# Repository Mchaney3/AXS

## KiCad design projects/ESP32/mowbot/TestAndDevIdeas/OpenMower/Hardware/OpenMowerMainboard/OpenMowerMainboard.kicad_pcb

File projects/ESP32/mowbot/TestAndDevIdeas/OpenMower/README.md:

# OpenMower

## Join the Discord server for OpenMower discussion: 

# About the Project
**:warning: DISCLAIMER:**

**IF YOU ARE NOT 100% SURE WHAT YOU ARE DOING, PLEASE DON'T TRY THIS AT HOME!**

**This repo is still WIP. The robot works though, I just need to make hardware and software pretty, so just :star: star and 👀 watch the repository if you want updates!**

Let's be honest: The current generation of robotic lawn mowers sucks. Basically all of these bots drive in a random direction until they hit the border of the lawn, rotate for a randomized duration and repeat. **I think we can do better!**

Therefore, we have disassembled the cheapest off-the-shelf robotic mower  we could find (YardForce Classic 500) and were surprised that the hardware itself is actually quite decent:
- Geared sensored brushless motors for the wheels
- A sensored brushless motor for the mower motor itself
- The whole construction seems robust, waterproof and all in all thought through
- All components are connected using standard connectors, therefore upgrading the hardware is easily possible.

The bottom line is: The bot itself is surprisingly high quality and doesn't need to be changed at all. **We just need some better software in there**.

# Project Goals

Here is a quick overview of this project's goals:

:heavy_check_mark: **Autonomous Lawn Mowing:** Obviously, the device should be able to mow the lawn automatically.

:heavy_check_mark: **Good Safety:** The device must be safe, e.g. emergency stop if lifted or crashed.

:heavy_check_mark: **No Perimeter Wire Needed:** We want to be flexible and support multiple mowing areas.

:heavy_check_mark: **Low Cost:** It should be cheaper than a mid range off-the-shelf product

:heavy_check_mark: **Open Source:** I want to share knowledge and enable others to build an OpenMower as well.

:heavy_check_mark: **Nice to Look At:** You should not be ashamed to have an OpenMower mowing your lawn.

:heavy_check_mark: **Avoid Obstacles:** The mower should detect obstacles and avoid them during mowing.

:heavy_check_mark: **Rain Detection:** The device should be able to detect bad weather conditions and pause mowing until they improve.

# Current State

It's not really *that easy* to upgrade the robot, since unfortunately the mainboard used by those bots is proprietary. Therefore the first step is to create a mainboard which then can be used to deploy some better software later on. This is what we are currently working on.

## Hardware

The first mainboard PCB is almost done. It currently looks like this:

### Hardware To-Do:

- [ ] Low Level Firmware Implementation
  - [x] Voltage / Current Sense
  - [x] Emergency Stop Button tracking
  - [x] IMU Communication
  - [x] Rain Sensor
  - [x] Charging State
  - [ ] Sound Module
  - [ ] UI Board Communication
  - [ ] Low Power Mode
- [ ] ROS Hardware Interface
- [ ] Hardware Redesign (bugs / enhancements):
  - [ ] Digial Emergency Stop Signal from Pico to xESC
  - [ ] Sound Module Pinout needs to be adapted to DFPlayer
  - [ ] XT60 Power Connector needs to be connected to main power instead of charging input

# Software

The basic software is basically done; Our prototype works as intended (but is not able to avoid obstacles yet).

The software for the robot can be found in a separate repository: https://github.com/ClemensElflein/open_mower_ros

### Software To-Do:

- [x] Mowing State Machine (Docking / Mowing, ...)
- [x] Path Planning
- [ ] Obstacle Avoidance
- [ ] App / Visualization

# How You Can Help

The project is currently much more advanced than it might currently look on this page. The prototype below is able to mow our lawn without problems. **But the documentation is missing.**

Therefore, at the current state, you can only wait until I have uploaded all code and documentation to this repository. **Star this repository in order to get updates!**

## Compatible Robotic Mowers

While disassembling the bot, I wondered about its mainboard: Instead of "YardForce" it read "GForce". After checking the internet for "GForce" robots, I found that that very similar looking robotic mowers are sold under the Herkules brand. Naturally I tried to dig deeper and actually found evidence that the mainboard is manufactured by some chinese company (SUMTEC Hardware).

It is therefore quite safe to assume that many robot mowers are **basically the same device in a different case**. This would be a huge win for the community, since this would mean that by making one of those robots smarter, we could upgrade **A LOT OF ROBOTS!**

Therefore it might be a good idea to start a list of compatible devices. So if you have a cheap robotic lawn mower, it would be nice of you to check, if it contains the same mainboard as ours and send me some pictures / model numbers.

# More Infos

This page only contains the basic overview of the project. To follow my current development state, check out my [Blog](https://x-tech.online/).

# License

<br />This work is licensed under a <a rel="license" href="http://creativecommons.org/licenses/by-nc-sa/4.0/">Creative Commons Attribution-NonCommercial-ShareAlike 4.0 International License</a>.

Feel free to use the design in your private/educational projects, but don't try to sell the design or products based on it without getting my consent first. The idea here is to share knowledge, not to enable others to simply sell my work. Thank you for understanding.

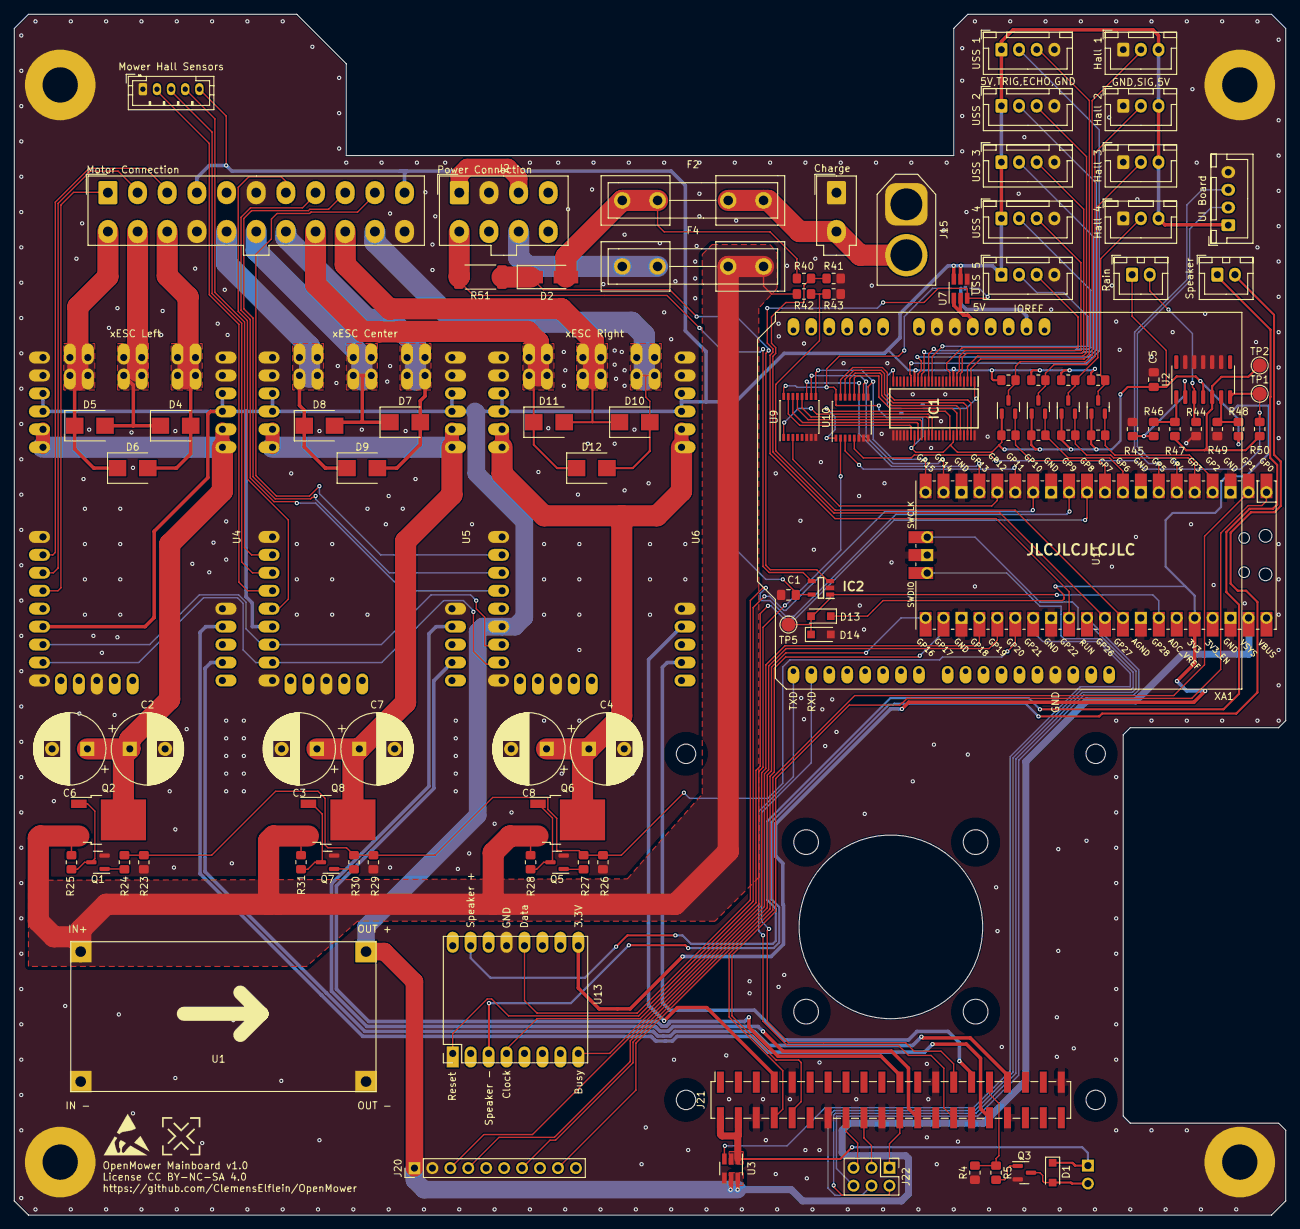
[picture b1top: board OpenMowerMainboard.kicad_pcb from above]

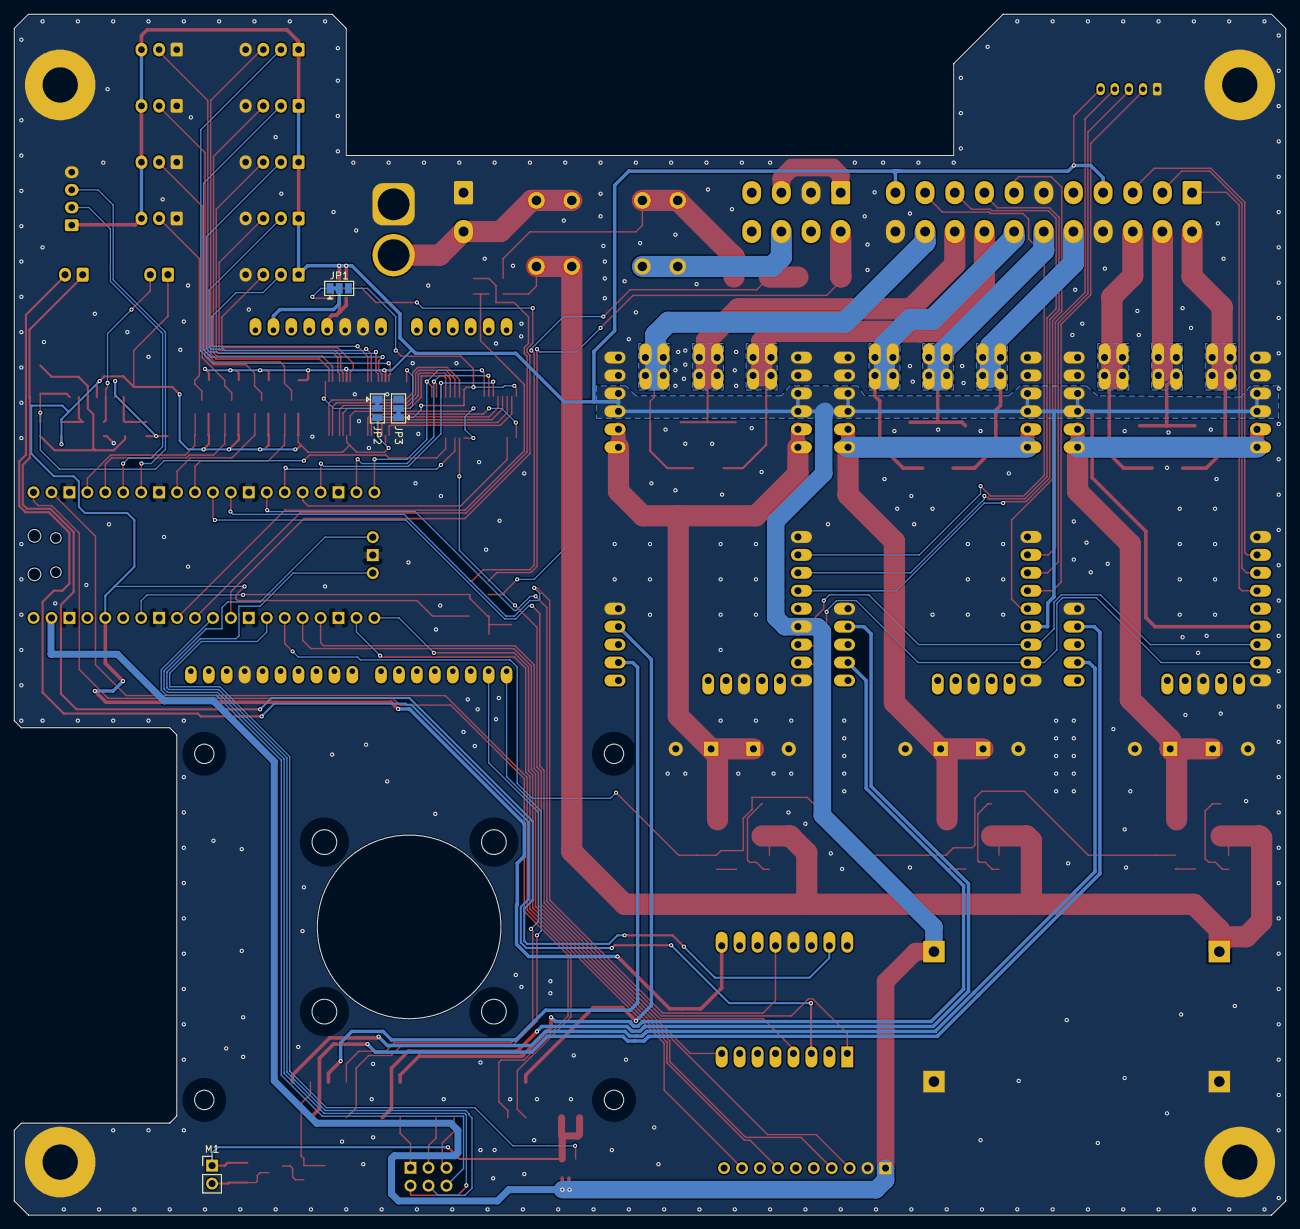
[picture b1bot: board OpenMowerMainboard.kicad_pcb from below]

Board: 2 copper layers, 180.0 x 170.0 mm, 110 parts (4 on the bottom side), 121 nets.

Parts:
C1, C5: 100n; C_0805_2012Metric_Pad1.18x1.45mm_HandSolder
C2, C3, C4, C6, C7, C8: C_Polarized; CP_Radial_D10.0mm_P5.00mm
D1, D13: D_Schottky; D_SOD-123F
D2: D_Schottky; D_SMA_Handsoldering
D4, D5, D6, D7, D8, D9, D10, D11, D12: D_TVS; D_SMB
D14: D_Zener; D_SOD-123F
F2, F4: Fuse; Fuseholder5x20_horiz_open_inline_Type-I
H1, H2, H3, H4: MountingHole_Pad; MountingHole_5mm_Pad
IC1: 74ALVC164245DGG,11; SOP50P810X120-48N
IC2: TSC101CILT; SOT95P280X145-5N
J1: Conn_02x11_Top_Bottom; Molex_Mini-Fit_Jr_5566-22A_2x11_P4.20mm_Vertical
J2: Conn_02x04_Top_Bottom; Molex_Mini-Fit_Jr_5566-08A_2x04_P4.20mm_Vertical
J3: Conn_01x02; Molex_Mini-Fit_Jr_5566-02A_2x01_P4.20mm_Vertical
J5, J6, J7, J8, J9, J19: Conn_01x04; JST_XH_B4B-XH-A_1x04_P2.50mm_Vertical
J10: Conn_01x05; JST_PH_B5B-PH-K_1x05_P2.00mm_Vertical
J11, J12, J13, J14: Conn_01x03_Male; JST_XH_B3B-XH-A_1x03_P2.50mm_Vertical
J15: Conn_01x02_Male; AMASS_XT60-M_1x02_P7.20mm_Vertical
J17, J18: Conn_01x02; JST_XH_B2B-XH-A_1x02_P2.50mm_Vertical
J20: Conn_01x10_Female; PinHeader_1x10_P2.54mm_Vertical
J21: Raspberry_Pi_2_3; PinSocket_2x20_P2.54mm_Vertical_SMD
J22: Conn_02x03_Odd_Even; PinHeader_2x03_P2.54mm_Vertical
JP1, JP2, JP3: SolderJumper_3_Bridged12; SolderJumper-3_P1.3mm_Bridged12_Pad1.0x1.5mm
M1: Fan; PinHeader_1x02_P2.54mm_Vertical
Q1, Q3, Q5, Q7, Q13, Q14, Q15, Q16: BSS138; SOT-23
Q2, Q6, Q8: Q_PMOS_GDS; TO-252-2
R3, R4, R5, R6, R9, R10, R15, R16, R19, R20, R23, R24, R25, R26, R27, R28, R29, R30, R31, R40, R41, R42, R43: R; R_0805_2012Metric_Pad1.20x1.40mm_HandSolder
R44, R46: 47k; R_0805_2012Metric_Pad1.20x1.40mm_HandSolder
R45: 1k; R_0805_2012Metric_Pad1.20x1.40mm_HandSolder
R47: 560; R_0805_2012Metric_Pad1.20x1.40mm_HandSolder
R48, R50: 10k; R_0805_2012Metric_Pad1.20x1.40mm_HandSolder
R49: 6.8k; R_0805_2012Metric_Pad1.20x1.40mm_HandSolder
R51: R; R_2512_6332Metric_Pad1.40x3.35mm_HandSolder
TP1, TP2, TP5: TestPoint; TestPoint_Pad_D2.0mm
U1: LM2596S_MODULE
U2: MCP604; SOIC-14_3.9x8.7mm_P1.27mm
U3, U7: SIP32509DT; SOT-23-6_Handsoldering
U4, U5, U6: xESC2
U9, U10: 74HC4051; SSOP-16_4.4x5.2mm_P0.65mm
U11: Pico; RPi_Pico_SMD_TH
U13: WTV020
XA1: Arduino_Uno_Shield

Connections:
+3V3: C5.2, D13.1 (K), IC1.31 (VCC(A)_1), IC1.42 (VCC(A)_2), J17.1, JP1.3 (B), JP2.3 (B), JP3.1 (A), Q13.1 (G), Q14.1 (G), Q15.1 (G), Q16.1 (G), R3.1, R9.1, R15.1, R19.1, R48.2, U2.4 (V+), U9.16 (VCC), U10.16 (VCC), U11.36 (3V3), U13.16 (VIN)
+5V: C1.1, IC1.7 (VCC(B)_1), IC1.18 (VCC(B)_2), IC2.5 (VCC), J1.4, J1.11, J5.1, J6.1, J7.1, J8.1, J9.1, J10.5, J11.3, J12.3, J13.3, J14.3, J19.1, J20.1, R6.1, R10.1, R16.1, R20.1, U1.3 (OUT+), U3.5 (VIN), U3.6 (VIN), U4.5V, U5.5V, U6.5V, U7.5 (VIN), U7.6 (VIN), U11.39 (VSYS)
/CHARGE_CURRENT: D13.2 (A), D14.1 (K), IC2.1 (OUT), TP5.1, U11.34 (GPIO28_ADC2)
/ESCs/MC_HALL_U: J10.2, U5.4 (HALL_U)
/ESCs/MC_HALL_V: J10.3, U5.5 (HALL_V)
/ESCs/MC_HALL_W: J10.4, U5.6 (HALL_W)
/ESCs/MC_PHASE_U: D7.2 (A2), D9.2 (A2), J1.18, U5.U
/ESCs/MC_PHASE_V: D7.1 (A1), D8.2 (A2), J1.17, U5.V
/ESCs/MC_PHASE_W: D8.1 (A1), D9.1 (A1), J1.16, U5.W
/ESCs/MC_POWER: R23.1, R24.1, R26.1, R27.1, R29.1, R30.1, U11.26 (GPIO20)
/ESCs/MC_RX: J21.24 (~CE0/GPIO8), U5.14 (NCS/RX)
/ESCs/MC_TEMP: J1.7, U5.3 (TEMPERATURE)
/ESCs/MC_TX: J21.21 (MISO0/GPIO9), U5.12 (MOSI/TX)
/ESCs/ML_HALL_U: J1.1, U4.4 (HALL_U)
/ESCs/ML_HALL_V: J1.2, U4.5 (HALL_V)
/ESCs/ML_HALL_W: J1.3, U4.6 (HALL_W)
/ESCs/ML_PHASE_U: D4.2 (A2), D6.2 (A2), J1.14, U4.U
/ESCs/ML_PHASE_V: D4.1 (A1), D5.2 (A2), J1.13, U4.V
/ESCs/ML_PHASE_W: D5.1 (A1), D6.1 (A1), J1.12, U4.W
/ESCs/ML_RX: J21.32 (PWM0/GPIO12), U4.14 (NCS/RX)
/ESCs/ML_TX: J21.33 (PWM1/GPIO13), U4.12 (MOSI/TX)
/ESCs/MOSFET_SWITCH1/VOUT: C4.1, C8.1, Q6.2 (D), U6.VM (VIN)
/ESCs/MOSFET_SWITCH2/VOUT: C3.1, C7.1, Q8.2 (D), U5.VM (VIN)
/ESCs/MOSFET_SWITCH/VOUT: C2.1, C6.1, Q2.2 (D), U4.VM (VIN)
/ESCs/MR_HALL_U: J1.8, U6.4 (HALL_U)
/ESCs/MR_HALL_V: J1.9, U6.5 (HALL_V)
/ESCs/MR_HALL_W: J1.10, U6.6 (HALL_W)
/ESCs/MR_PHASE_U: D10.2 (A2), D12.2 (A2), J1.21, U6.U
/ESCs/MR_PHASE_V: D10.1 (A1), D11.2 (A2), J1.20, U6.V
/ESCs/MR_PHASE_W: D11.1 (A1), D12.1 (A1), J1.19, U6.W
/ESCs/MR_RX: J21.7 (GCLK0/GPIO4), U6.14 (NCS/RX)
/ESCs/MR_TX: J21.29 (GCLK1/GPIO5), U6.12 (MOSI/TX)
/GPS/GPS_POWER: U7.1 (VOUT), U7.2 (VOUT), XA1.5V1 (5V)
/GPS/POWER_EN: JP1.1 (A), U7.3 (ENABLE), U11.29 (GPIO22)
/GPS/RXD: J21.27 (ID_SD/GPIO0), XA1.D1 (D1_TX0)
/GPS/TXD: J21.28 (ID_SC/GPIO1), XA1.D0 (D0_RX0)
/IMU/MISO: J20.7, U11.21 (GPIO16)
/IMU/MOSI: J20.4, U11.25 (GPIO19)
/IMU/SCK: J20.3, U11.24 (GPIO18)
/IMU/~CS: J20.9, U11.22 (GPIO17)
/RAIN_DETECTED: R50.2, TP1.1, U2.7, U10.5 (A5)
/RaspberryPi/PICO_RESET: J22.6, U11.30 (RUN)
/RaspberryPi/PICO_SWCLK: J22.2, U11.41 (SWCLK)
/RaspberryPi/PICO_SWDIO: J22.4, U11.43 (SWDIO)
/RaspberryPi/POWER_EN: U3.3 (ENABLE), U11.27 (GPIO21)
/RaspberryPi/RASPI_FAN_ON: J21.31 (GCLK2/GPIO6), R4.2, R5.1
/RaspberryPi/RASPI_POWER: D1.1 (K), J21.2 (5V), J21.4 (5V), M1.1 (+), U3.1 (VOUT), U3.2 (VOUT)
/RaspberryPi/UART0_RXD: J21.10 (GPIO15/RXD), U11.1 (GPIO0)
/RaspberryPi/UART0_TXD: J21.8 (GPIO14/TXD), U11.2 (GPIO1)
/RobotConnectors/CHARGE_SHUNT_MINUS: IC2.4 (VM), J2.5, R51.2
/RobotConnectors/CHARGE_SHUNT_PLUS: D2.1 (K), IC2.3 (VP), R51.1
/RobotConnectors/HALL_SWITCH_1: Q13.2 (S), R3.2, U11.10 (GPIO7)
/RobotConnectors/HALL_SWITCH_1_5V: J11.2, Q13.3 (D), R6.2
/RobotConnectors/HALL_SWITCH_2: Q14.2 (S), R9.2, U11.9 (GPIO6)
/RobotConnectors/HALL_SWITCH_2_5V: J12.2, Q14.3 (D), R10.2
/RobotConnectors/HALL_SWITCH_3: Q15.2 (S), R15.2, U11.5 (GPIO3)
/RobotConnectors/HALL_SWITCH_3_5V: J13.2, Q15.3 (D), R16.2
/RobotConnectors/HALL_SWITCH_4: Q16.2 (S), R19.2, U11.4 (GPIO2)
/RobotConnectors/HALL_SWITCH_4_5V: J14.2, Q16.3 (D), R20.2
/RobotConnectors/LED_RX: J19.2, U11.6 (GPIO4)
/RobotConnectors/LED_TX: J19.3, U11.7 (GPIO5)
/RobotConnectors/RAIN-: J17.2, R44.2, U2.3 (+)
/RobotConnectors/SPEAKER_MINUS: J18.2, U13.5 (SPEAKER-)
/RobotConnectors/SPEAKER_PLUS: J18.1, U13.4 (SPEAKER+)
/RobotConnectors/USS_1_ECHO: IC1.47 (1A0), U10.15 (A2)
/RobotConnectors/USS_1_ECHO_5V: IC1.2 (1B0), J5.3
/RobotConnectors/USS_1_TRIGGER: IC1.30 (2A4), U9.15 (A2)
/RobotConnectors/USS_1_TRIGGER_5V: IC1.19 (2B4), J5.2
/RobotConnectors/USS_2_ECHO: IC1.46 (1A1), U10.14 (A1)
/RobotConnectors/USS_2_ECHO_5V: IC1.3 (1B1), J6.3
/RobotConnectors/USS_2_TRIGGER: IC1.32 (2A3), U9.14 (A1)
/RobotConnectors/USS_2_TRIGGER_5V: IC1.17 (2B3), J6.2
/RobotConnectors/USS_3_ECHO: IC1.44 (1A2), U10.13 (A0)
/RobotConnectors/USS_3_ECHO_5V: IC1.5 (1B2), J7.3
/RobotConnectors/USS_3_TRIGGER: IC1.33 (2A2), U9.13 (A0)
/RobotConnectors/USS_3_TRIGGER_5V: IC1.16 (2B2), J7.2
/RobotConnectors/USS_4_ECHO: IC1.43 (1A3), U10.12 (A3)
/RobotConnectors/USS_4_ECHO_5V: IC1.6 (1B3), J8.3
/RobotConnectors/USS_4_TRIGGER: IC1.35 (2A1), U9.12 (A3)
/RobotConnectors/USS_4_TRIGGER_5V: IC1.14 (2B1), J8.2
/RobotConnectors/USS_5_ECHO: IC1.41 (1A4), U10.1 (A4)
/RobotConnectors/USS_5_ECHO_5V: IC1.8 (1B4), J9.3
/RobotConnectors/USS_5_TRIGGER: IC1.36 (2A0), U9.1 (A4)
/RobotConnectors/USS_5_TRIGGER_5V: IC1.13 (2B0), J9.2
/RobotConnectors/V_CHARGE: D2.2 (A), F2.1, R40.2
/pico/MUX_ADDRESS_0: U9.11 (S0), U10.11 (S0), U11.17 (GPIO13)
/pico/MUX_ADDRESS_1: U9.10 (S1), U10.10 (S1), U11.19 (GPIO14)
/pico/MUX_ADDRESS_2: U9.9 (S2), U10.9 (S2), U11.20 (GPIO15)
/pico/MUX_INPUT: U10.3 (A), U11.15 (GPIO11)
/pico/MUX_OUTPUT: U9.3 (A), U11.16 (GPIO12)
/pico/SOUND_BUSY: U10.2 (A6), U13.15 (BUSY)
/pico/SOUND_CLK: U11.11 (GPIO8), U13.7 (CLK)
/pico/SOUND_DATA: U11.12 (GPIO9), U13.10 (Data)
/pico/SOUND_RESET: U11.14 (GPIO10), U13.1 (RESET)
/pico/V_CHARGE: R40.1, R41.2, U11.31 (GPIO26_ADC0)
/pico/V_IN: R42.1, R43.2, U11.32 (GPIO27_ADC1)
GND: C1.2, C2.2, C3.2, C4.2, C5.1, C6.2, C7.2, C8.2, D14.2 (A), H1.1, H2.1, H3.1, H4.1, IC1.4 (GND_1), IC1.10 (GND_2), IC1.15 (GND_3), IC1.21 (GND_4), IC1.25 (~2OE), IC1.26 (2A7), IC1.27 (2A6), IC1.28 (GND_5), IC1.29 (2A5), IC1.34 (GND_6), IC1.39 (GND_7), IC1.45 (GND_8), IC1.48 (~1OE), IC2.2 (GND), J1.6, J1.15, J1.22, J2.2, J3.1, J5.4, J6.4, J7.4, J8.4, J9.4, J10.1, J11.1, J12.1, J13.1, J14.1, J15.1, J19.4, J20.2, J21.6 (GND), J21.9 (GND), J21.14 (GND), J21.20 (GND), J21.25 (GND), J21.30 (GND), J21.34 (GND), J21.39 (GND), JP2.1 (A), JP3.3 (B), Q1.2 (S), Q3.2 (S), Q5.2 (S), Q7.2 (S), R4.1, R23.2, R26.2, R29.2, R41.1, R43.1, R44.1, R45.1, R49.2, U1.1 (IN-), U1.4 (OUT-), U2.9 (-), U2.10 (+), U2.11 (V-), U2.12 (+), U2.13 (-), U3.4 (GND), U4.GND, U5.GND, U6.GND, U7.4 (GND), U9.6 (~E), U9.7 (VEE), U9.8 (GND), U10.6 (~E), U10.7 (VEE), U10.8 (GND), U11.3 (GND), U11.8 (GND), U11.13 (GND), U11.18 (GND), U11.23 (GND), U11.28 (GND), U11.33 (AGND), U11.38 (GND), U11.42 (GND), U13.8 (GND), XA1.GND1 (GND), XA1.GND2 (GND), XA1.GND3 (GND)
unnamed: D1.2 (A), M1.2 (-), Q3.3 (D)
unnamed: F2.2, J3.2, J15.2
unnamed: F4.1, J2.7
unnamed: IC1.1 (1DIR), JP2.2 (C)
unnamed: IC1.24 (2DIR), JP3.2 (C)
unnamed: J2.1, J2.3
unnamed: J21.16 (GPIO23), J22.5
unnamed: J21.18 (GPIO24), J22.3
unnamed: J21.22 (GPIO25), J22.1
unnamed: JP1.2 (C), XA1.IORF (IOREF)
unnamed: Q1.1 (G), R24.2
unnamed: Q1.3 (D), Q2.1 (G), R25.2
unnamed: Q3.1 (G), R5.2
unnamed: Q5.1 (G), R27.2
unnamed: Q5.3 (D), Q6.1 (G), R28.2
unnamed: Q7.1 (G), R30.2
unnamed: Q7.3 (D), Q8.1 (G), R31.2
unnamed: R45.2, R46.2, U2.2 (-)
unnamed: R46.1, R47.1, U2.1
unnamed: R47.2, R50.1, TP2.1, U2.5 (+)
unnamed: R48.1, R49.1, U2.6 (-)
unnamed: U4.1 (CAN_L), U5.1 (CAN_L), U6.1 (CAN_L)
unnamed: U4.2 (CAN_H), U5.2 (CAN_H), U6.2 (CAN_H)
V_BATT: F4.2, Q2.3 (S), Q6.3 (S), Q8.3 (S), R25.1, R28.1, R31.1, R42.2, U1.2 (IN+)

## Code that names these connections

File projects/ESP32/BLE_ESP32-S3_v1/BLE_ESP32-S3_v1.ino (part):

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******************************    PINS USED     *******************************
   
  //  Motors
  int motorForwardPin =  5; //GPIO5
  int motorBackwardPin = 6; //GPIO6
  
  //  Voltage Sensor
  const int batteryVOLTAGE = 7; // Use GPIO number. See ESP32 board pinouts
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  Chip Select       8
  
  //  Software SPI Pins
  SPID = MOSI = GPIO11 = data out
  SPIQ = MISO = GPIO13 = data in
  CLK = GPIO12
  CS = GPIO10

  //  Ws2812B
  int ledPIN = 48;
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//Timer
#define _TIMERINTERRUPT_LOGLEVEL_     4
#include "ESP32TimerInterrupt.h"
#define PIN_D2              4         // Pin D2 mapped to pin GPIO2/ADC12/TOUCH2/LED_BUILTIN of ESP32
#define PIN_D3              5         // Pin D3 mapped to pin GPIO3/RX0 of ESP32
*/
//BLE
#include <BLEDevice.h>
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const char deviceName[] = "OS Railway";

//Voltage Sensor
const int batteryVOLTAGE = 4; // //GPIO7

//Motor
int motorForwardPin = 5; //GPIO5
int motorBackwardPin = 6; //GPIO6
int motorSpeed = 0;  //PWM value to initialize motors with
String rx_MotorDirection = "";
String motorForward = "true";
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#define SS 10  //  Hardware Chip Select Pin

/*
  SPID = MOSI = GPIO11 = data out
  SPIQ = MISO = GPIO13 = data in
  CLK = GPIO12
  CS = GPIO10
*/

// Chip select may be constant or RAM variable.
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
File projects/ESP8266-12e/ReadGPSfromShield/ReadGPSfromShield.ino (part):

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    - D5 (ESP32) --> 7 (shield's RST)
    - D18 (ESP32) --> 6 (shield's PWRKEY)
    - Also make sure to connect a 3.7V LiPo battery to the shield's JST connector!!!
    - Optional: SCL (GPIO22) and SDA (GPIO21) if you want to use the temperature sensor

    Note that you can change the pin definitions to use TX1/RX1 but some ESP32 dev boards do not have these pins
    broken out (like the DOIT ESP32 dev board, for example). You can also change the TX/RX pins to pretty much
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// For botletics SIM7000 shield with ESP32
#define FONA_PWRKEY 18
#define FONA_RST 5
#define FONA_TX 2 // ESP32 hardware serial RX2 (GPIO16)
#define FONA_RX 8 // ESP32 hardware serial TX2 (GPIO17)

// For botletics SIM7500 shield
//#define FONA_PWRKEY 6
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
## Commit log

2023-09-09 Reconciling Repo's
2024-12-04 Adding ROS Project
2024-12-11 Repo Cleanup
2025-01-09 Project Updates
2025-01-09 Repo Updates

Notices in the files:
projects/ESP8266-12e/ReadGPSfromShield/ReadGPSfromShield.ino:
License: GNU GPL v3.0
BSD license, all text above must be included in any redistribution
projects/ESP32/mowbot/TestAndDevIdeas/OpenMower/Hardware/OpenMowerMainboard/OpenMowerMainboard.kicad_pcb:
License CC BY-NC-SA 4.0
